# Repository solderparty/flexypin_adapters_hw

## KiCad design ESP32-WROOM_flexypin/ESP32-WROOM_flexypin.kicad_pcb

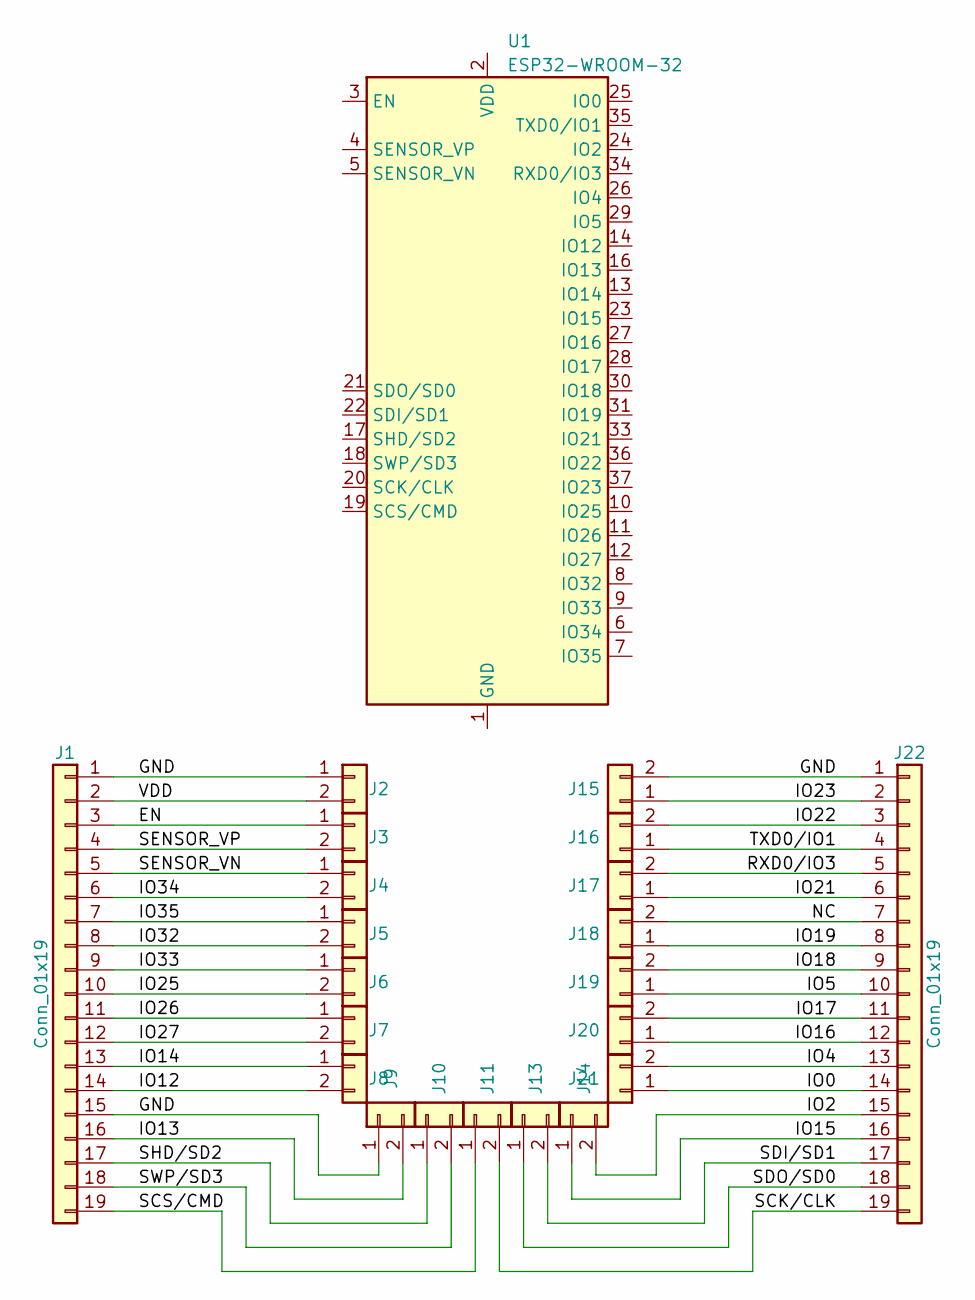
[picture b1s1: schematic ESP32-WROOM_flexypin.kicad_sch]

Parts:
J1, J22: Conn_01x19; PinHeader_1x19_P2.54mm_Vertical
J2, J3, J4, J5, J6, J7, J8, J9, J10, J11, J13, J14, J15, J16, J17, J18, J19, J20, J21: Conn_01x02; FlexyPin_1x02_P1.27mm
U1: ESP32-WROOM-32

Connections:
/EN: J1.3, J3.1
/GND: J1.1, J1.15, J2.1, J9.1, J15.2, J22.1
/IO0: J21.1, J22.14
/IO2: J14.2, J22.15
/IO4: J21.2, J22.13
/IO5: J19.1, J22.10
/IO12: J1.14, J8.2
/IO13: J1.16, J9.2
/IO14: J1.13, J8.1
/IO15: J14.1, J22.16
/IO16: J20.1, J22.12
/IO18: J19.2, J22.9
/IO19: J18.1, J22.8
/IO21: J17.1, J22.6
/IO22: J16.2, J22.3
/IO23: J15.1, J22.2
/IO25: J1.10, J6.2
/IO26: J1.11, J7.1
/IO27: J1.12, J7.2
/IO32: J1.8, J5.2
/IO33: J1.9, J6.1
/IO34: J1.6, J4.2
/IO35: J1.7, J5.1
/NC: J18.2, J22.7
/RXD0/IO3: J17.2, J22.5
/SCK/CLK: J11.2, J22.19
/SCS/CMD: J1.19, J11.1
/SDI/SD1: J13.2, J22.17
/SDO/SD0: J13.1, J22.18
/SENSOR_VN: J1.5, J4.1
/SENSOR_VP: J1.4, J3.2
/SHD/SD2: J1.17, J10.1
/SWP/SD3: J1.18, J10.2
/TXD0/IO1: J16.1, J22.4
/VDD: J1.2, J2.2
unnamed: J20.2, J22.11
unnamed: U1.1 (GND), U1.15 (GND), U1.38 (GND), U1.39 (GND)

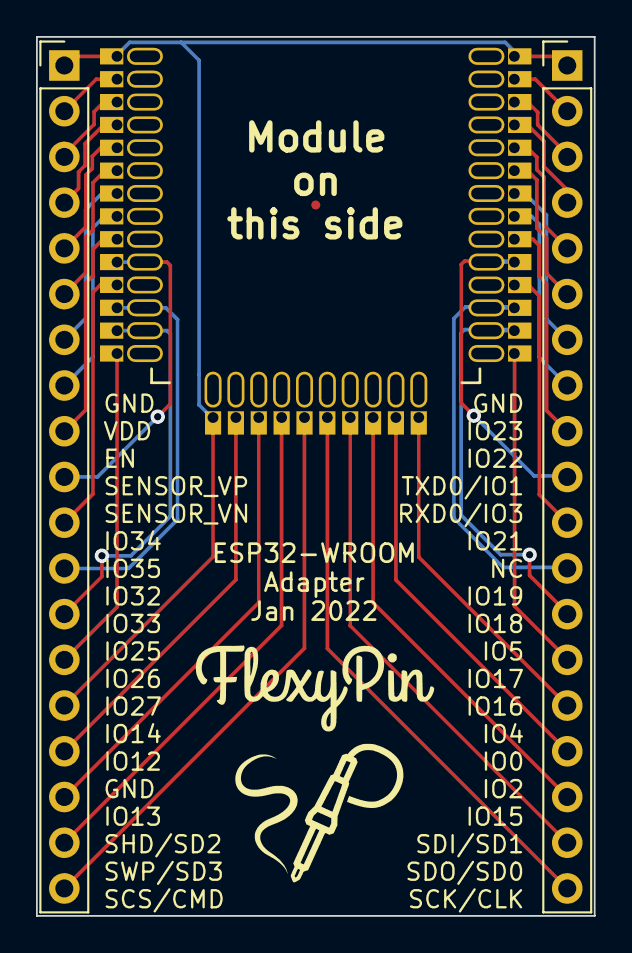
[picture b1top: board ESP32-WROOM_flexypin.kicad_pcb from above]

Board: 2 copper layers, 31.0 x 48.8 mm, 21 parts (0 on the bottom side), 36 nets.

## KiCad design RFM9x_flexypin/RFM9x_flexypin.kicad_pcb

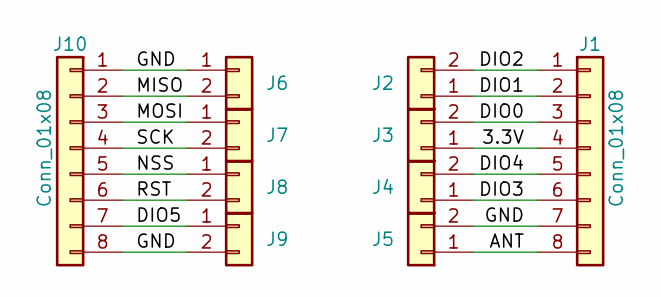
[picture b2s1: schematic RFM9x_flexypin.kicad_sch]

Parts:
J1, J10: Conn_01x08; PinHeader_1x08_P2.54mm_Vertical
J2, J3, J4, J5, J6, J7, J8, J9: Conn_01x02; FlexyPin_1x02_P2.00mm

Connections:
/3.3V: J1.4, J3.1
/ANT: J1.8, J5.1
/DIO0: J1.3, J3.2
/DIO1: J1.2, J2.1
/DIO2: J1.1, J2.2
/DIO3: J1.6, J4.1
/DIO4: J1.5, J4.2
/DIO5: J9.1, J10.7
/GND: J1.7, J5.2, J6.1, J9.2, J10.1, J10.8
/MISO: J6.2, J10.2
/MOSI: J7.1, J10.3
/NSS: J8.1, J10.5
/RST: J8.2, J10.6
/SCK: J7.2, J10.4

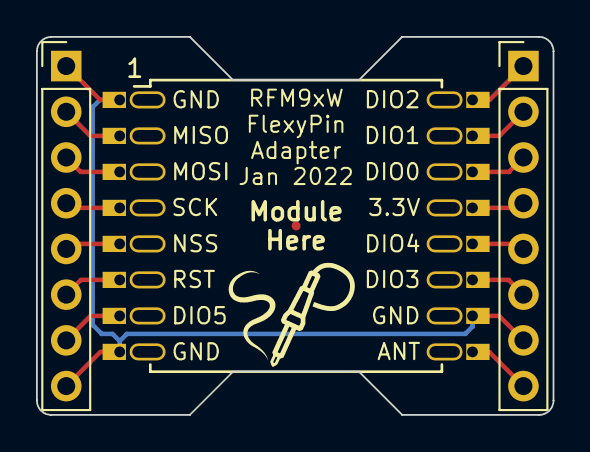
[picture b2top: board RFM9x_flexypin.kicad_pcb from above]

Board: 2 copper layers, 28.7 x 21.0 mm, 10 parts (0 on the bottom side), 14 nets.
